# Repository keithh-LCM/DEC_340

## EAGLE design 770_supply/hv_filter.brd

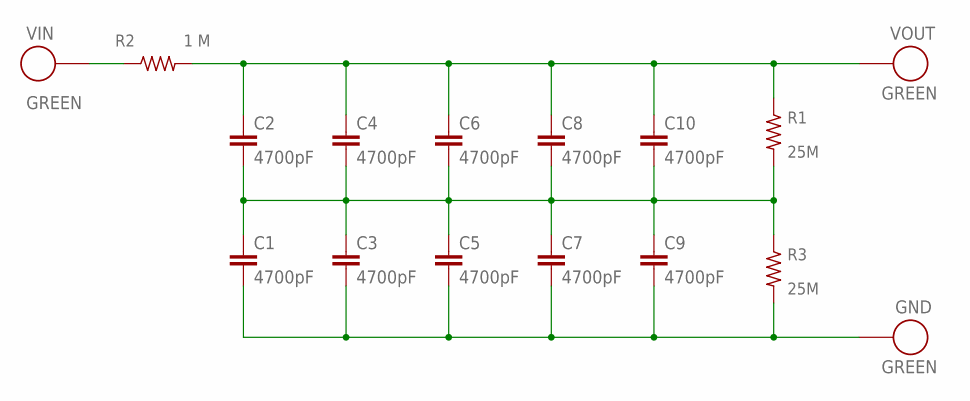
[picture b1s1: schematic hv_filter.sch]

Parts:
C1, C2, C3, C4, C5, C6, C7, C8, C9, C10: 4700pF; 4700PF6KV
GND: GREEN; AWG22
R1, R3: 25M; 25MOHM
R2: 1 M; 1M20KV
VIN: GREEN; AWG22
VOUT: GREEN; AWG22

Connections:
unnamed: R2.P$1, VIN.P$1
unnamed: C2.P$1 (1), C4.P$1 (1), C6.P$1 (1), C8.P$1 (1), C10.P$1 (1), R1.P$1, R2.P$2, VOUT.P$1
unnamed: C1.P$1 (1), C2.P$2 (2), C3.P$1 (1), C4.P$2 (2), C5.P$1 (1), C6.P$2 (2), C7.P$1 (1), C8.P$2 (2), C9.P$1 (1), C10.P$2 (2), R1.P$2, R3.P$1
unnamed: C1.P$2 (2), C3.P$2 (2), C5.P$2 (2), C7.P$2 (2), C9.P$2 (2), GND.P$1, R3.P$2

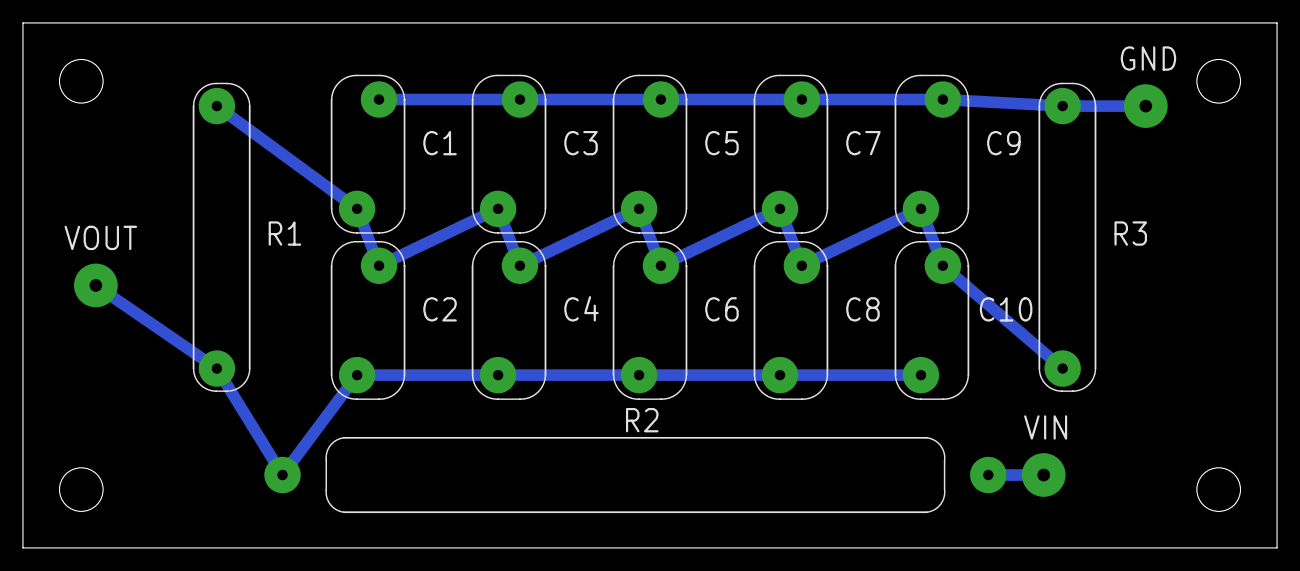
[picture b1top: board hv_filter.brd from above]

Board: 2 copper layers, 109.2 x 45.7 mm, 16 parts (0 on the bottom side), 4 nets.

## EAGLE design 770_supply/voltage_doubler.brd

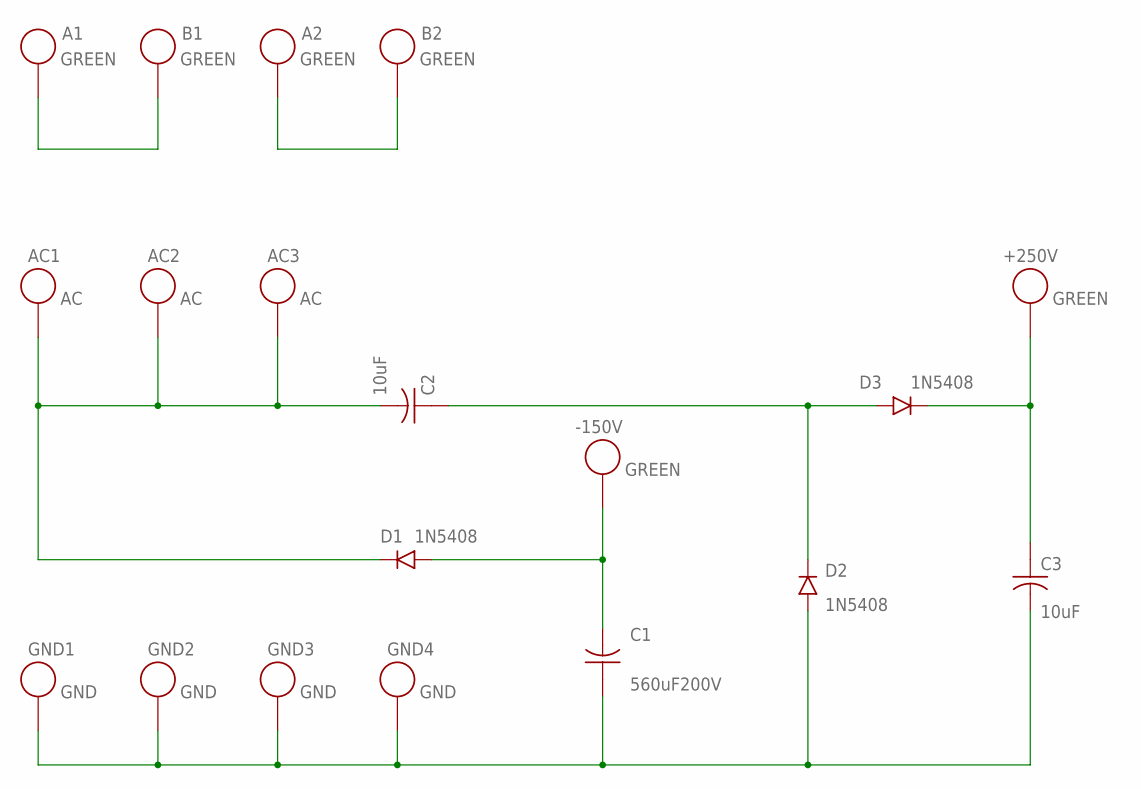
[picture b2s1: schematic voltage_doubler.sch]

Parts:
+250V: GREEN; AWG22
-150V: GREEN; AWG22
A1, A2: GREEN; AWG22
AC1, AC2, AC3: AC; AWG22
B1, B2: GREEN; AWG22
C1: 560uF200V; WIREDCAP
C2, C3: 10uF; AXIAL10UF400V
D1, D2, D3: 1N5408; DO-201AD
GND1, GND2, GND3, GND4: GND; AWG22

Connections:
unnamed: -150V.P$1, C1.P$2 (2), D1.A
unnamed: AC1.P$1, AC2.P$1, AC3.P$1, C2.P$2 (2), D1.C
unnamed: C1.P$1 (1), C3.P$2 (2), D2.A, GND1.P$1, GND2.P$1, GND3.P$1, GND4.P$1
unnamed: C2.P$1 (1), D2.C, D3.A
unnamed: +250V.P$1, C3.P$1 (1), D3.C
unnamed: A2.P$1, B2.P$1
unnamed: A1.P$1, B1.P$1

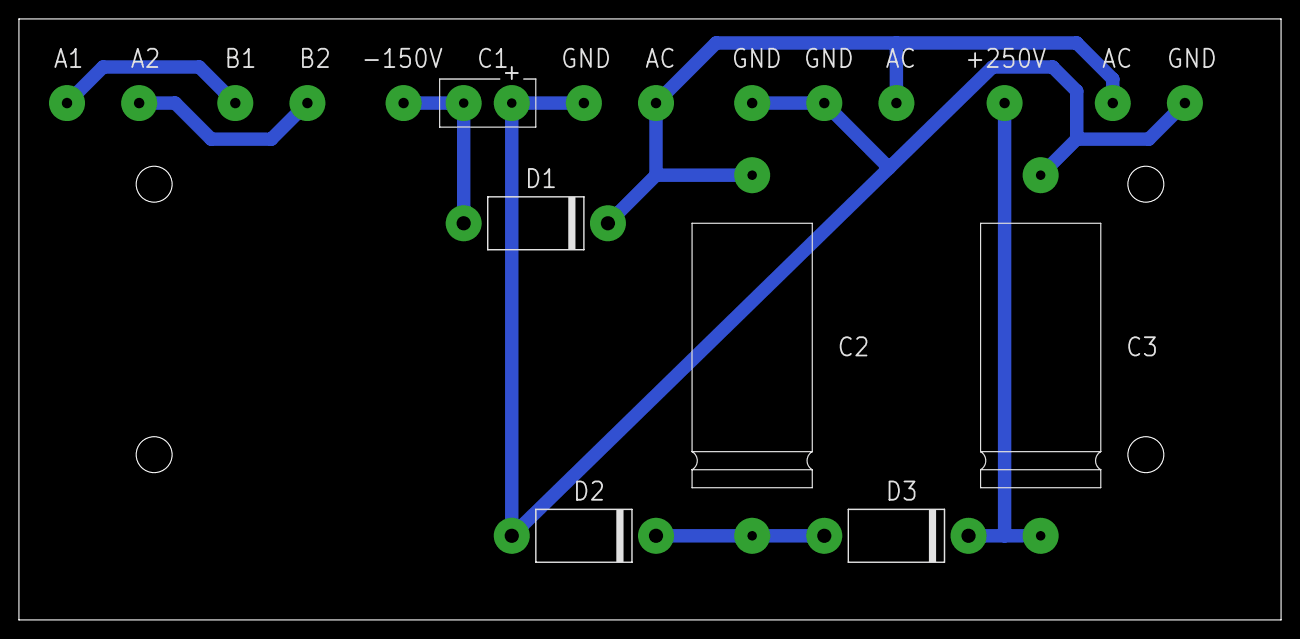
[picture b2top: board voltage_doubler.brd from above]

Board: 2 copper layers, 133.3 x 63.5 mm, 19 parts (0 on the bottom side), 7 nets.

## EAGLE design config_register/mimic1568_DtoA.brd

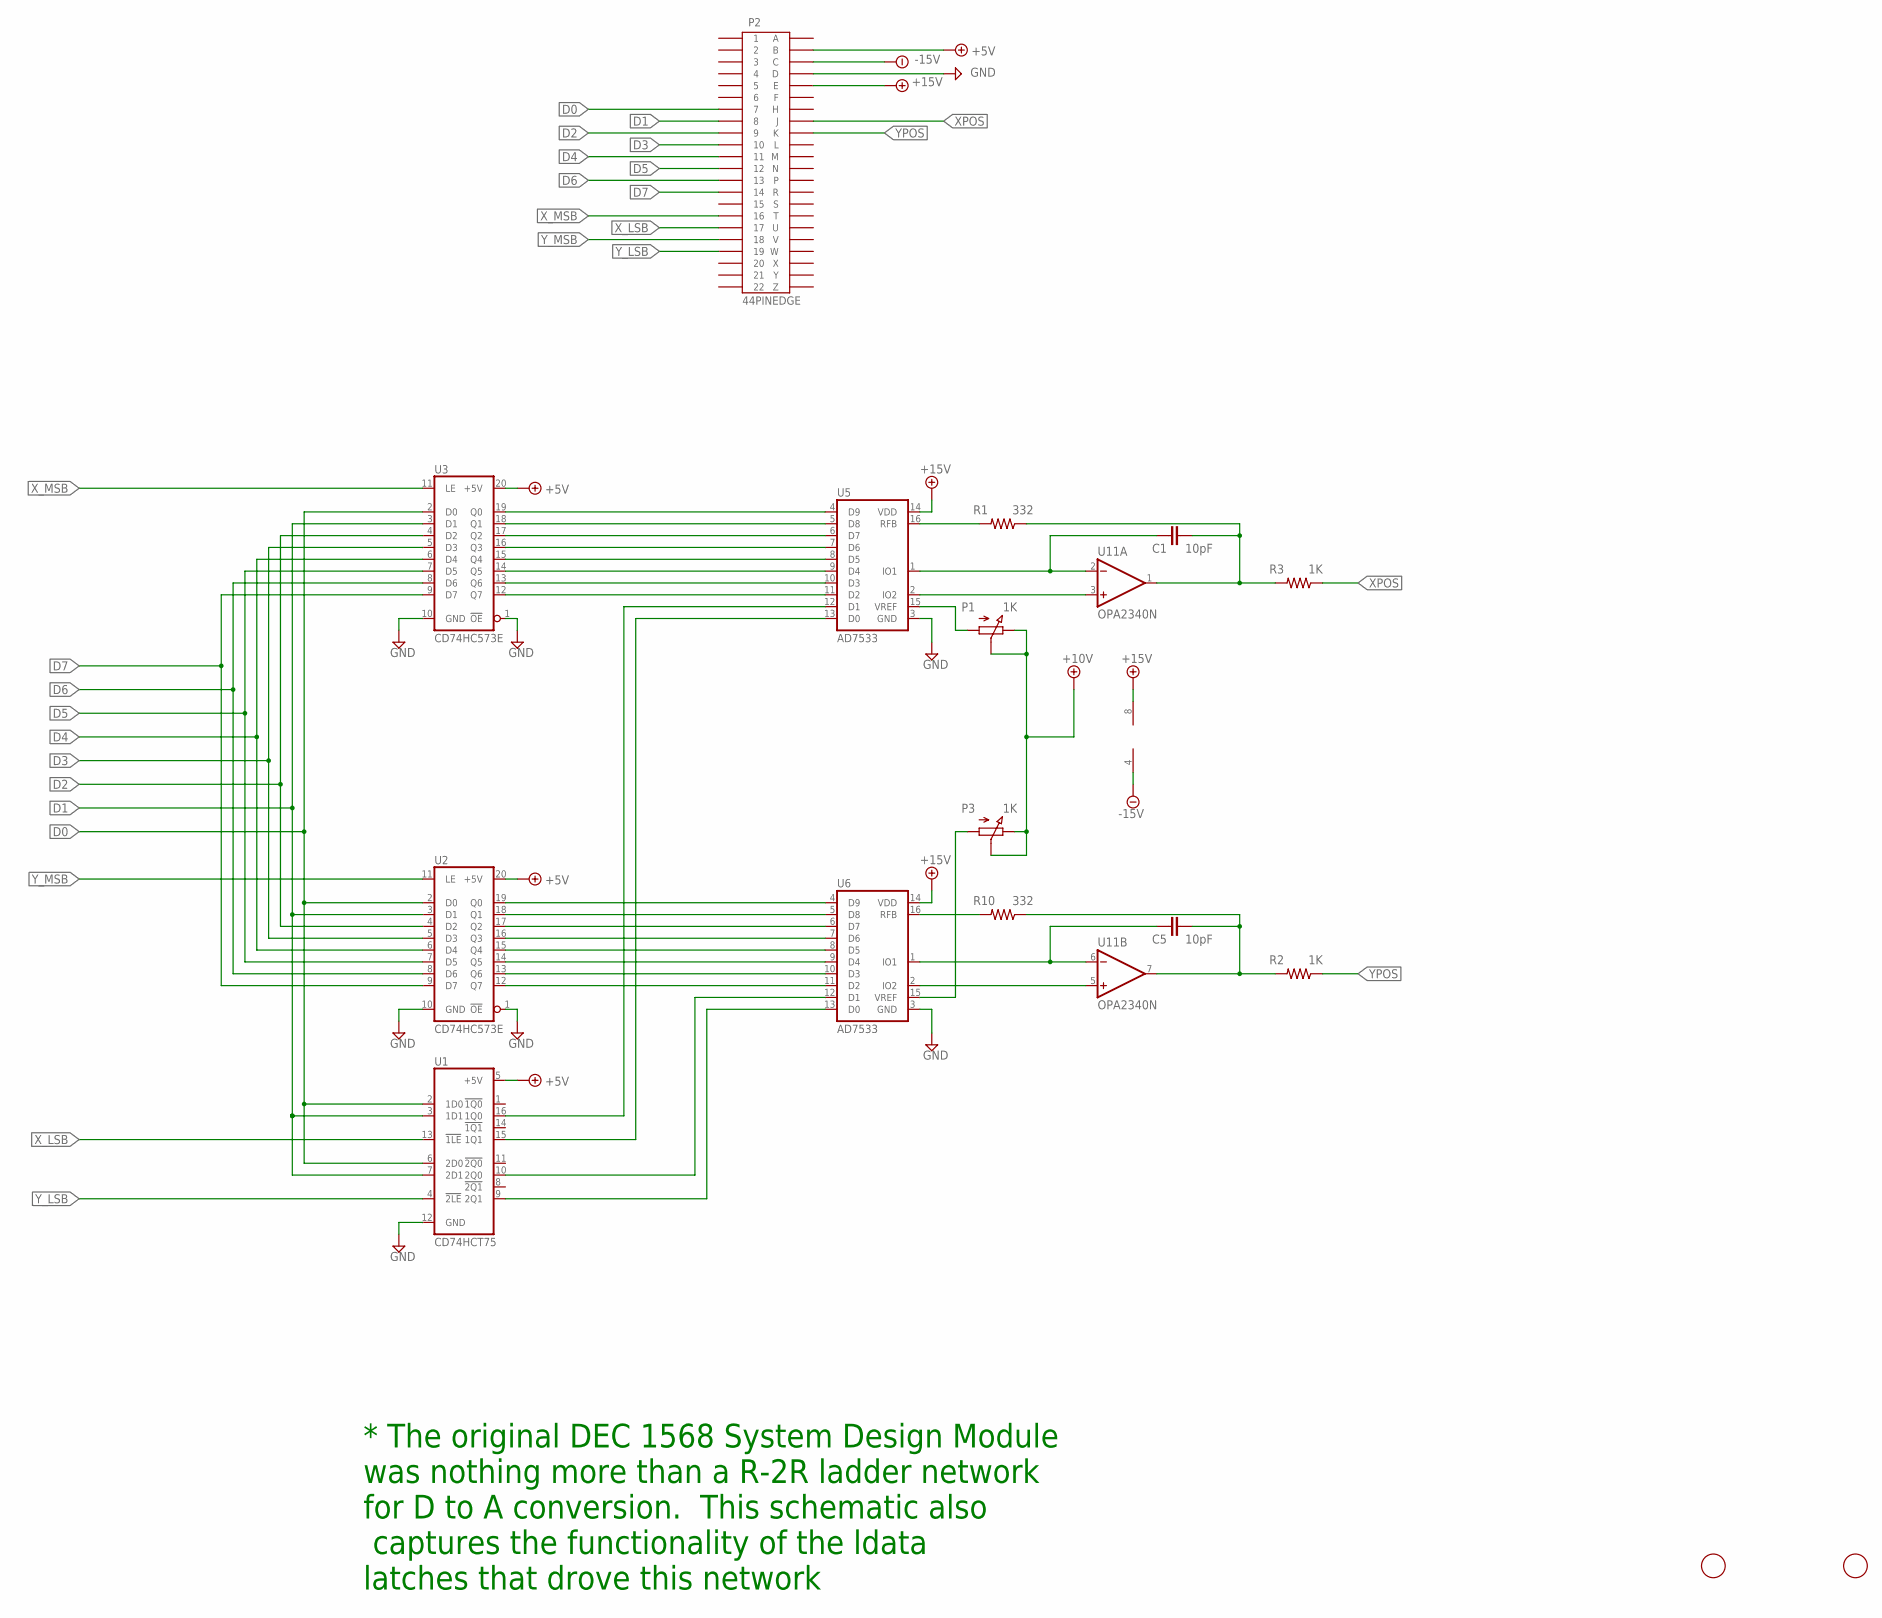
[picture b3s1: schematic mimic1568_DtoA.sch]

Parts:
C1, C5: 10pF; C2.5
P1, P3: 1K; 3006P
P2: 44PINEDGE
R1, R10: 332; 0207/10
R2, R3: 1K; 0207/10
U1: CD74HCT75; DIP-16
U2, U3: CD74HC573E; DIP-20
U5, U6: AD7533; DIP-16
U11: OPA2340N; DIP-08
U$1, U$2: FIDUCIAL; FIDUCIAL_1MM

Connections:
+5V: P2.B, U1.5 (+5V), U2.20 (+5V), U3.20 (+5V)
+10V: P1.2 (S), P1.3 (E), P3.2 (S), P3.3 (E)
+15V: P2.E, U5.14 (VDD), U6.14 (VDD), U11.8 (V+)
-15V: P2.C, U11.4 (V-)
D0: P2.7, U1.2 (1D0), U1.6 (2D0), U2.2 (D0), U3.2 (D0)
D1: P2.8, U1.3 (1D1), U1.7 (2D1), U2.3 (D1), U3.3 (D1)
D2: P2.9, U2.4 (D2), U3.4 (D2)
D3: P2.10, U2.5 (D3), U3.5 (D3)
D4: P2.11, U2.6 (D4), U3.6 (D4)
D5: P2.12, U2.7 (D5), U3.7 (D5)
D6: P2.13, U2.8 (D6), U3.8 (D6)
D7: P2.14, U2.9 (D7), U3.9 (D7)
GND: P2.D, U1.12 (GND), U2.1 (!OE), U2.10 (GND), U3.1 (!OE), U3.10 (GND), U5.3 (GND), U6.3 (GND)
unnamed: U1.9 (2Q1), U6.13 (D0)
unnamed: U1.16 (1Q0), U5.12 (D1)
unnamed: U1.15 (1Q1), U5.13 (D0)
unnamed: C1.1, U5.1 (IO1), U11.2 (-IN)
unnamed: U5.2 (IO2), U11.3 (+IN)
unnamed: U2.19 (Q0), U6.4 (D9)
unnamed: U2.18 (Q1), U6.5 (D8)
unnamed: U2.17 (Q2), U6.6 (D7)
unnamed: U2.16 (Q3), U6.7 (D6)
unnamed: U2.15 (Q4), U6.8 (D5)
unnamed: U2.14 (Q5), U6.9 (D4)
unnamed: U2.13 (Q6), U6.10 (D3)
unnamed: U2.12 (Q7), U6.11 (D2)
unnamed: C1.2, R1.1, R3.2, U11.1 (OUT)
unnamed: P1.1 (A), U5.15 (VREF)
unnamed: U3.19 (Q0), U5.4 (D9)
unnamed: U3.18 (Q1), U5.5 (D8)
unnamed: U3.17 (Q2), U5.6 (D7)
unnamed: U3.16 (Q3), U5.7 (D6)
unnamed: U3.15 (Q4), U5.8 (D5)
unnamed: U3.14 (Q5), U5.9 (D4)
unnamed: U3.13 (Q6), U5.10 (D3)
unnamed: U3.12 (Q7), U5.11 (D2)
unnamed: U1.10 (2Q0), U6.12 (D1)
unnamed: R1.2, U5.16 (RFB)
unnamed: C5.2, R2.2, R10.1, U11.7 (OUT)
unnamed: C5.1, U6.1 (IO1), U11.6 (-IN)
unnamed: U6.2 (IO2), U11.5 (+IN)
unnamed: R10.2, U6.16 (RFB)
unnamed: P3.1 (A), U6.15 (VREF)
XPOS: P2.J, R3.1
X_LSB: P2.17, U1.13 (!1LE)
X_MSB: P2.16, U3.11 (LE)
YPOS: P2.K, R2.1
Y_LSB: P2.19, U1.4 (!2LE)
Y_MSB: P2.18, U2.11 (LE)

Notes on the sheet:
* The original DEC 1568 System Design Module was nothing more than a R-2R ladder network for D to A conversion. This schematic also captures the functionality of the ldata latches that drove this network

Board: 2 copper layers, 17 parts (0 on the bottom side), 49 nets, no tracks yet.

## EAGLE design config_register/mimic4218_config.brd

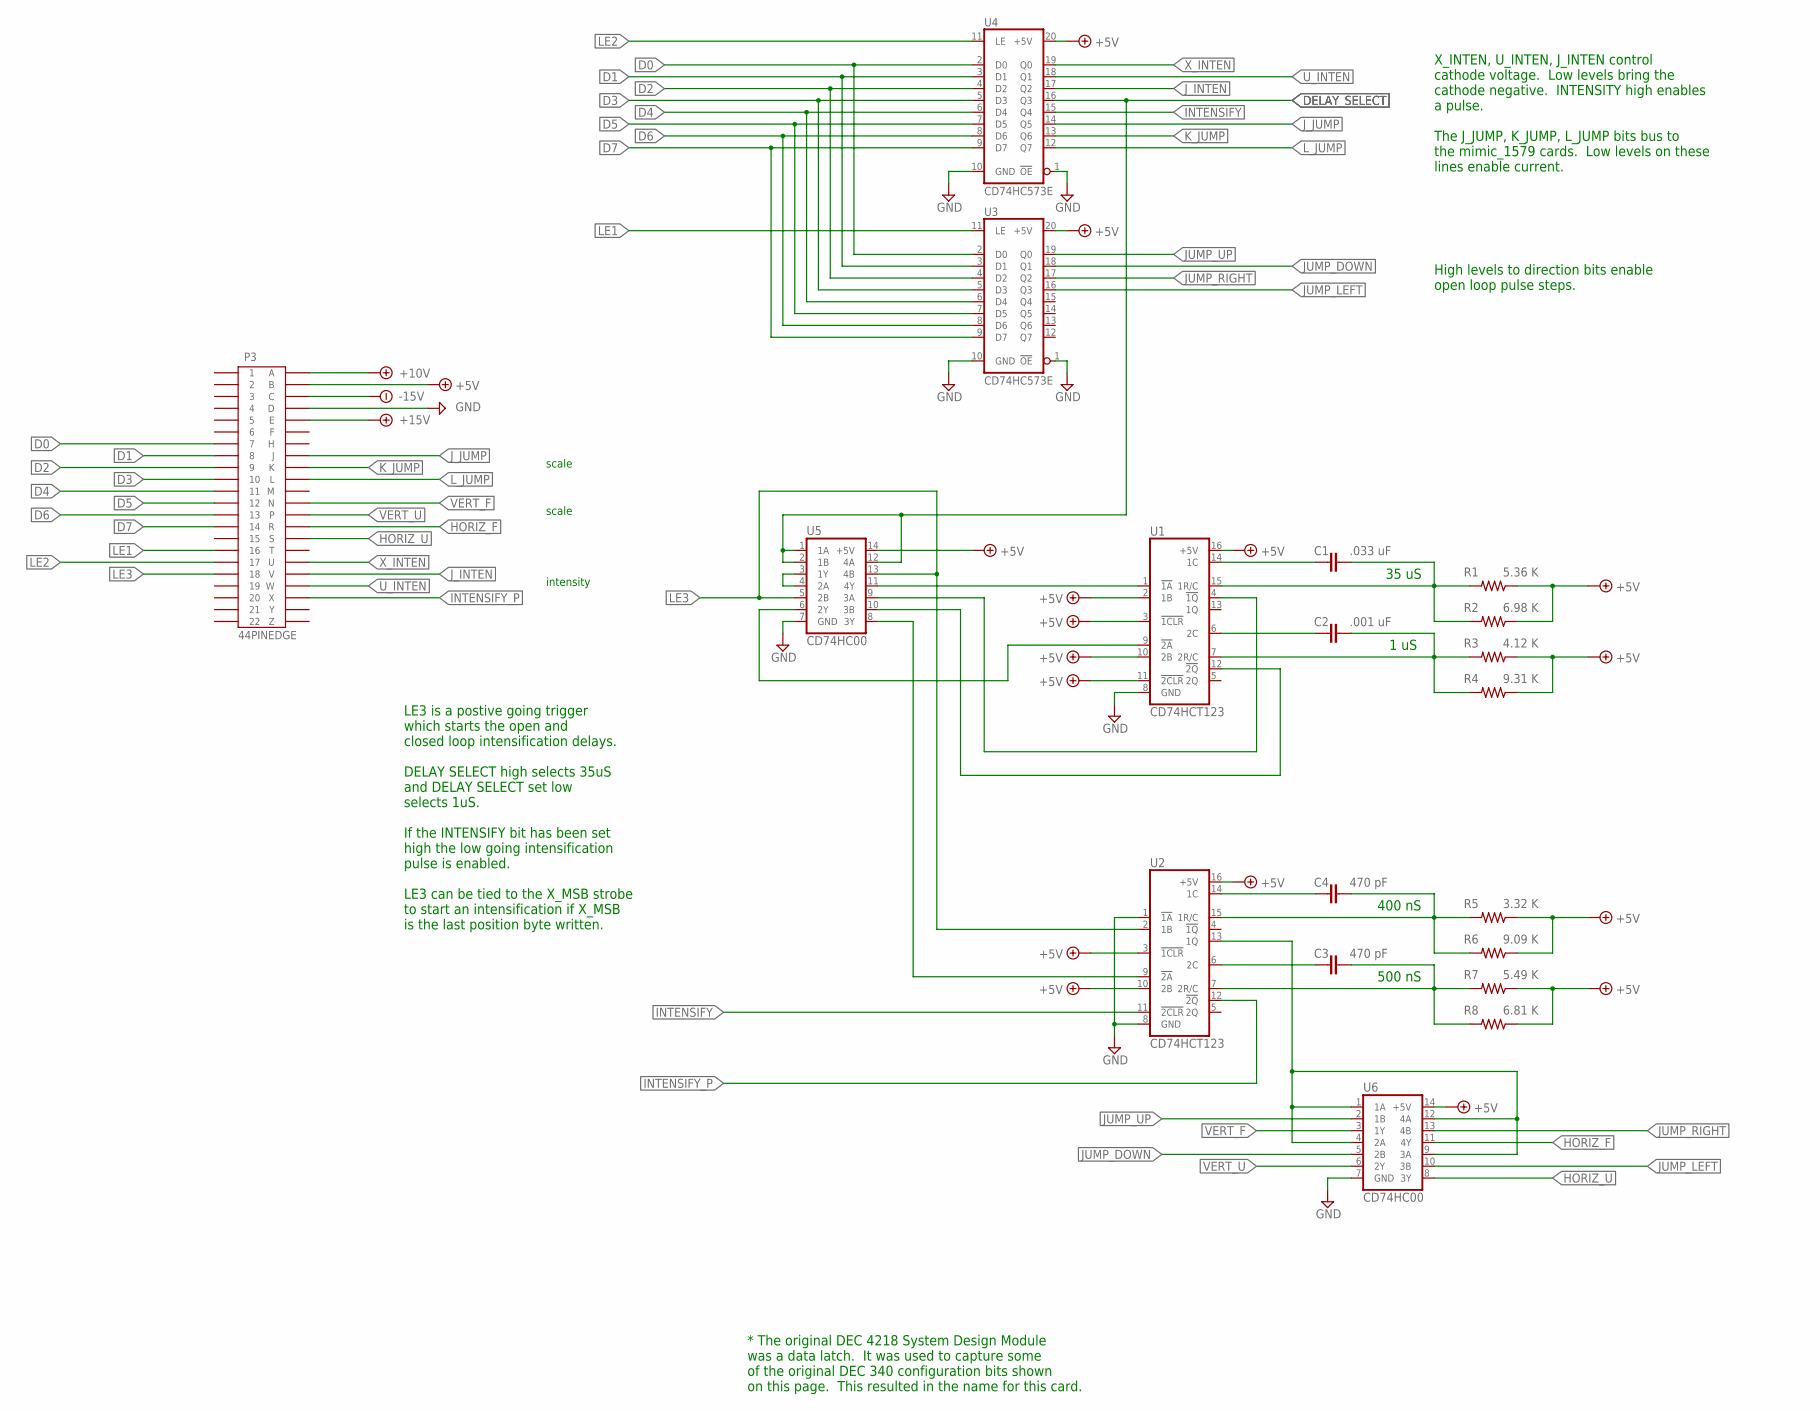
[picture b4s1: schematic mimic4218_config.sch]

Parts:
C1: .033 uF; 5MM_TH
C2: .001 uF; 5MM_TH
C3, C4: 470 pF; 5MM_TH
P3: 44PINEDGE
R1: 5.36 K; 0207/10
R2: 6.98 K; 0207/10
R3: 4.12 K; 0207/10
R4: 9.31 K; 0207/10
R5: 3.32 K; 0207/10
R6: 9.09 K; 0207/10
R7: 5.49 K; 0207/10
R8: 6.81 K; 0207/10
U1, U2: CD74HCT123; DIP-16
U3, U4: CD74HC573E; DIP-20
U5, U6: CD74HC00; DIP-14

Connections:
+5V: P3.B, R1.1, R2.1, R3.1, R4.1, R5.1, R6.1, R7.1, R8.1, U1.2 (1B), U1.3 (!1CLR), U1.10 (2B), U1.11 (!2CLR), U1.16 (+5V), U2.3 (!1CLR), U2.10 (2B), U2.16 (+5V), U3.20 (+5V), U4.20 (+5V), U5.14 (+5V), U6.14 (+5V)
+10V: P3.A
+15V: P3.E
-15V: P3.C
D0: P3.7, U3.2 (D0), U4.2 (D0)
D1: P3.8, U3.3 (D1), U4.3 (D1)
D2: P3.9, U3.4 (D2), U4.4 (D2)
D3: P3.10, U3.5 (D3), U4.5 (D3)
D4: P3.11, U3.6 (D4), U4.6 (D4)
D5: P3.12, U3.7 (D5), U4.7 (D5)
D6: P3.13, U3.8 (D6), U4.8 (D6)
D7: P3.14, U3.9 (D7), U4.9 (D7)
DELAY_SELECT: U4.16 (Q3), U5.1 (1A), U5.2 (1B), U5.12 (4A)
GND: P3.D, U1.8 (GND), U2.1 (!1A), U2.8 (GND), U3.1 (!OE), U3.10 (GND), U4.1 (!OE), U4.10 (GND), U5.7 (GND), U6.7 (GND)
HORIZ_F: P3.R, U6.11 (4Y)
HORIZ_U: P3.S, U6.8 (3Y)
INTENSIFY: U2.11 (!2CLR), U4.15 (Q4)
INTENSIFY_P: P3.X, U2.12 (!2Q)
JUMP_DOWN: U3.18 (Q1), U6.5 (2B)
JUMP_LEFT: U3.16 (Q3), U6.10 (3B)
JUMP_RIGHT: U3.17 (Q2), U6.13 (4B)
JUMP_UP: U3.19 (Q0), U6.2 (1B)
J_INTEN: P3.V, U4.17 (Q2)
J_JUMP: P3.J, U4.14 (Q5)
K_JUMP: P3.K, U4.13 (Q6)
LE1: P3.16, U3.11 (LE)
LE2: P3.17, U4.11 (LE)
LE3: P3.18, U2.2 (1B), U5.5 (2B), U5.13 (4B)
L_JUMP: P3.L, U4.12 (Q7)
unnamed: C1.1, U1.14 (1C)
unnamed: C1.2, R1.2, R2.2, U1.15 (1R/C)
unnamed: C2.1, U1.6 (2C)
unnamed: C2.2, R3.2, R4.2, U1.7 (2R/C)
unnamed: C4.1, U2.14 (1C)
unnamed: C3.2, R7.2, R8.2, U2.7 (2R/C)
unnamed: C3.1, U2.6 (2C)
unnamed: C4.2, R5.2, R6.2, U2.15 (1R/C)
unnamed: U1.1 (!1A), U5.11 (4Y)
unnamed: U5.3 (1Y), U5.4 (2A)
unnamed: U2.13 (1Q), U6.1 (1A), U6.4 (2A), U6.9 (3A), U6.12 (4A)
unnamed: U1.9 (!2A), U5.6 (2Y)
unnamed: U1.4 (!1Q), U5.9 (3A)
unnamed: U1.12 (!2Q), U5.10 (3B)
unnamed: U2.9 (!2A), U5.8 (3Y)
U_INTEN: P3.W, U4.18 (Q1)
VERT_F: P3.N, U6.3 (1Y)
VERT_U: P3.P, U6.6 (2Y)
X_INTEN: P3.U, U4.19 (Q0)

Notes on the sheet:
35 uS
1 uS
500 nS
400 nS
* The original DEC 4218 System Design Module was a data latch. It was used to capture some of the original DEC 340 configuration bits shown on this page. This resulted in the name for this card.
High levels to direction bits enable open loop pulse steps.
X_INTEN, U_INTEN, J_INTEN control cathode voltage. Low levels bring the cathode negative. INTENSITY high enables a pulse. The J_JUMP, K_JUMP, L_JUMP bits bus to the mimic_1579 cards. Low levels on these lines enable current.
intensity
scale
LE3 is a postive going trigger which starts the open and closed loop intensification delays. DELAY SELECT high selects 35uS and DELAY SELECT set low selects 1uS. If the INTENSIFY bit has been set high the low going intensification pulse is enabled. LE3 can be tied to the X_MSB strobe to start an in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

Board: 2 copper layers, 19 parts (0 on the bottom side), 45 nets, no tracks yet.

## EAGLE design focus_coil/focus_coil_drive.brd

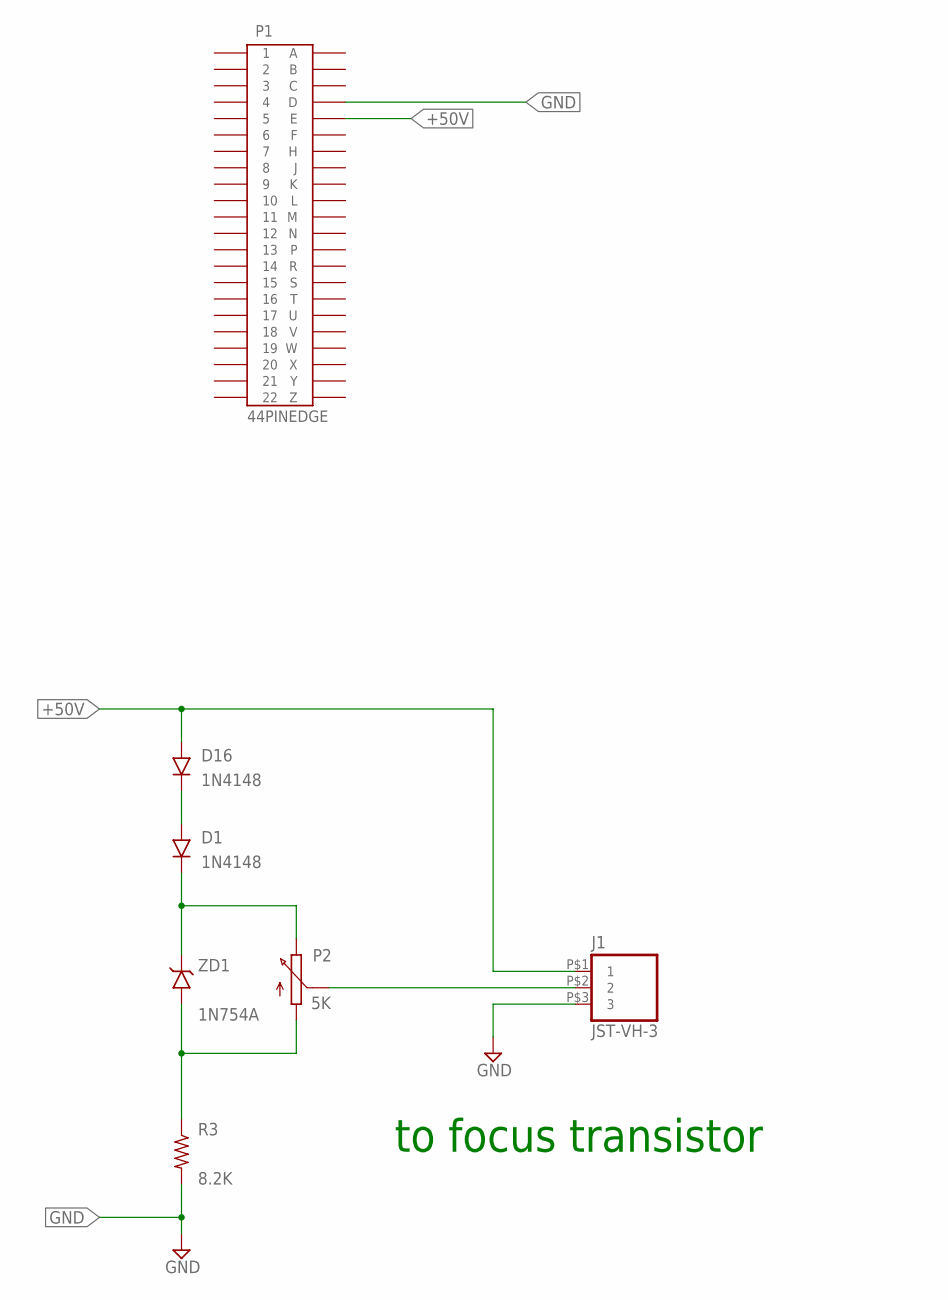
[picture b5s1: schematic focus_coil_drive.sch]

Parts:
D1, D16: 1N4148; DO35-7
J1: JST-VH-3; VHR-3N
P1: 44PINEDGE
P2: 5K; 3006P
R3: 8.2K; 0207/10
ZD1: 1N754A; DO35-7

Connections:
+50V: D16.A, J1.P$1 (1), P1.E
BASE: J1.P$2 (2), P2.2 (S)
GND: J1.P$3 (3), P1.D, R3.2
unnamed: D1.A, D16.C
unnamed: D1.C, P2.3 (E), ZD1.C
unnamed: P2.1 (A), R3.1, ZD1.A

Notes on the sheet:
to focus transistor

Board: 2 copper layers, 7 parts (0 on the bottom side), 6 nets, no tracks yet.

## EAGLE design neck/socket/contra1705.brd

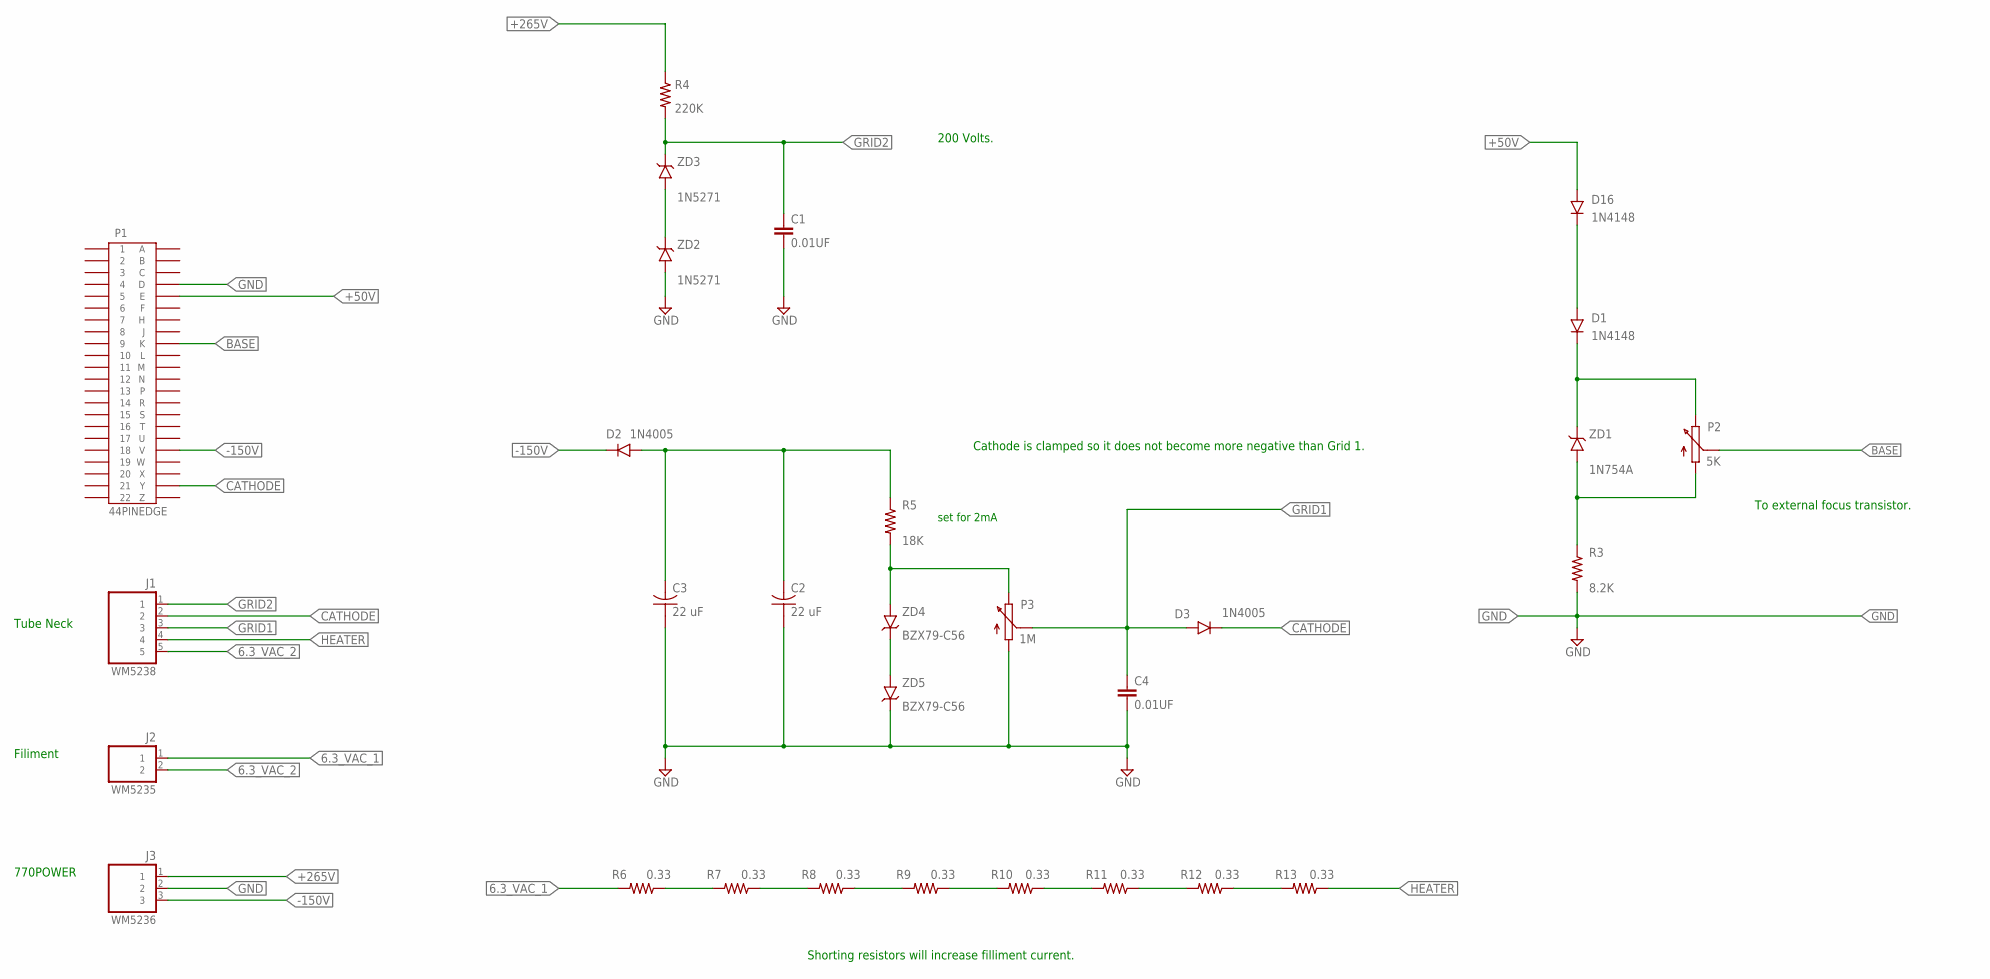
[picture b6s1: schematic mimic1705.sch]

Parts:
C1, C4: 0.01UF; 5MM_TH
C2, C3: 22 uF; AXIAL10X26
D1, D16: 1N4148; DO35-7
D2, D3: 1N4005; DO-41-10
J1: WM5238; MOLEX-WM5238
J2: WM5235; MOLEX-WM5235
J3: WM5236; MOLEX-WM5236
P1: 44PINEDGE
P2: 5K; 3006P
P3: 1M; 3006P
R3: 8.2K; 0207/10
R4: 220K; 0207/10
R5: 18K; 0207/10
R6, R7, R8, R9, R10, R11, R12, R13: 0.33; 0309/12
ZD1: 1N754A; DO35-7
ZD2, ZD3: 1N5271; DO35-7
ZD4, ZD5: BZX79-C56; DO35-7

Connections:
6.3_VAC_1: J2.1, R6.2
6.3_VAC_2: J1.5, J2.2
+50V: D16.A, P1.E
+265V: J3.1, R4.1
-150V: D2.C, J3.3, P1.V
BASE: P1.K, P2.2 (S)
CATHODE: D3.C, J1.2, P1.Y
GND: C1.2, C2.P$1 (1), C3.P$1 (1), C4.2, J3.2, P1.D, P3.1 (A), R3.2, ZD2.A, ZD5.C
GRID1: C4.1, D3.A, J1.3, P3.2 (S)
GRID2: C1.1, J1.1, R4.2, ZD3.C
HEATER: J1.4, R13.1
unnamed: ZD4.C, ZD5.A
unnamed: ZD2.C, ZD3.A
unnamed: D1.C, P2.3 (E), ZD1.C
unnamed: D1.A, D16.C
unnamed: R6.1, R7.2
unnamed: P2.1 (A), R3.1, ZD1.A
unnamed: P3.3 (E), R5.2, ZD4.A
unnamed: C2.P$2 (2), C3.P$2 (2), D2.A, R5.1
unnamed: R7.1, R8.2
unnamed: R8.1, R9.2
unnamed: R9.1, R10.2
unnamed: R10.1, R11.2
unnamed: R11.1, R12.2
unnamed: R12.1, R13.2

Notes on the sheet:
Filiment
770POWER
Tube Neck
set for 2mA
Cathode is clamped so it does not become more negative than Grid 1.
200 Volts.
To external focus transistor.
Shorting resistors will increase filliment current.

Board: 2 copper layers, 30 parts (0 on the bottom side), 25 nets, no tracks yet.
